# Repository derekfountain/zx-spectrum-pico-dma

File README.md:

# zx-spectrum-pico-dma

The Z80 CPU inside the ZX Spectrum is capable of DMA transfers. i.e. an external
device can take control of the buses and directly read and write the Spectrum's
memory.

To the best of my knowledge, no interface from the Spectrum's commercial era ever
took advantage of this feature, probably because it's a rather fussy thing to
work with. I wondered if it was possible for a modern microcontroller to do it.
Hence this project.

Answer: yes, it can.

# Two implementations

My first attempt at getting this DMA idea to work used my ZX Diagnostics Board
as a test platform. The fundamental problem is that an RP2040-based Pico doesn't
have enough GPIOs to do this sort of task. (It has 26, the Z80's address and data
buses immediately account for 24 of them.) I got it to work, but synchronising
the dual Picos was too slow and fussy. I eventually gave up on that and designed
a new Spectrum interface based on the RP2350B microcontroller.

The dual Pico approach is documented towards the end of this page. It's probably
not of much interest to most people. The RP2350B implementation is the more
interesting one. So let's start there.

## RP2350B Implementation

My second attempt at getting this to work involved a Raspberry Pi RP2350B microcontroller,
which has 48 GPIOs. Unlike the original RP2040, this is plenty enough for this sort of
project. I used a [Pimoroni Stamp XL](https://shop.pimoroni.com/products/rp2350-stamp-xl?variant=53521688002939).

### The Hardware

I designed a board and had it made up. It looks like this:

It's very simple, the Stamp XL runs off 5V so doesn't need any extra circuitry other
than a transistor to control the Z80's RESET line.

The RP2350 can handle the Spectrum's 5V signals as direct inputs to the GPIOs, so
the design is just to link pretty much everything on the Spectrum's rear edge connector
to a GPIO pin. The rest can be done in software.

### The Contention Problem

One of the primary reasons this DMA approach has rarely, if ever, been seen on a
Spectrum interface is the contention problem. The Spectrum's display is
generated by the ULA based on data it finds in the lower 16K of RAM. In order
to do that the ULA needs to be able to read that data from the 4116 DRAM
chips. But those chips are single ported, which means if the ULA and Z80 try
to read and/or write them simultaneously contention will happen, the ULA 
will get delayed or corrupted data, and the screen display will glitch.

The solution to this in the Spectrum circuitry is to have the ULA stop the
Z80's clock while the ULA is reading the screen memory. This solution would
also be required of any circuit which uses DMA to read or write the screen
memory. That is, if an external device takes control of the buses in order
to read or write to the screen memory, that device needs to stay clear of
the ULA's screen memory accesses otherwise contention becomes a problem.

### Timings

To do a DMA transfer into screen memory (0x4000 to 0x5AFF inclusive) it needs
to be timed precisely with the Spectrum's ULA hardware. The Spectrum hardware
in this area is simple and limited. The ULA emits a signal named INT
(because it's connected to the Z80's interrupt line) every 20ms. It does so when
the hardware is about to start drawing the screen and the TV raster is at the
top left corner.

So yes, that's simple, but it's also limited, because that's the only timing
signal the Spectrum emits. I have to work with that.

### Challenge 1 - Get it working

The initial challenge, then, is to get DMA working on the Spectrum. The aim here
is to write a single byte of data into the top left corner of the screen, with
everything else remaining stable and glitch free.

I'm going to put a dotted line - value 0x55 - in location 0x4000, so 4 little
dots appear in the corner.

### Approach

The approach used for this experimentation is as follows:

* RP2350 will raise a bus request, then wait for the Z80 to yield the buses and
respond with bus acknowledge
* RP2350 will put the address 0x4000 on the address bus
* RP2350 will put the value 0x55 on the data bus
* RP2350 will drive the signal lines in sequence to force a memory write
* RP2350 will then release the bus request signal and the Z80 can go back to
doing whatever it was doing

Compared the dual-Pico approach (scroll down if you want to know) this is pretty
straightforward, and works fine.

The key point is with the timing: this is going to happen while the ULA is
drawing the top border. Contention doesn't happen when the ULA is in 
"border time", only when the ULA is drawing the data part of the screen.
So if the DMA work can be done during border time there's no need to worry
about contention.

The other question is how long the buses need to be driven for. The first version
of my software controlled the signals with the same timing the Z80 uses. It
watched the CLK signal and responded to rising and falling clocks exactly as the
Z80 does (according to the timing diagrams in the Z80 manual). But that's not
necessary. Signals on the buses and control lines (like /MREQ and /WR) get to the
4116 DRAM chips via the Spectrum's ULA and multiplexers which pass the signals
in small numbers of nanoseconds. The 4116s themselves are the slow points, being
rated at completing a read or write in 150ns. It turns out that adding a delay
of 35 RP2350 "NOP" instructions between the /WR signal going active and inactive
is the minium requirement for successful writes. On a 150MHz RP2350 35 of the
single-cycle "NOP" instructions complete in 233ns, which seems a slower than it
needs to be. I need to investigate this. My test Spectrum for this project has been
one with a static RAM-based lower memory module, so it's hard to draw conclusions
from this hardware.

### Result

There's no point is trying to do this on an emulator, so screenshots are photos
from a real Spectrum screen.

Here's the result of the single byte write:

It's fuzzy and blurry, but, take my word for it, it does show what it should:
that splat in the in the top left corner is actually 4 individual dots. It sits
there permanently. Tapping ENTER clears the screen, but the dots flicker and
reappear immediately. They're being replaced every 20ms.

There's no way to stop this from the Z80 end. The BUSREQ/BUSACK mechanism on
the Z80 is highest priority, higher than NMI, even. If I do something on the
Spectrum which disables interrupts, the dots appear there anyway. The BEEP
command still plays a note, but it's a bit "buzzy."

### Transferring a Screenful of Data

The question that needed answering here was whether the DMA transfer would be fast
enough to move a whole ZX Spectrum display frame of data (6,912 bytes) from the RP2350
into the Spectrum's display memory in the time it takes the ULA to draw the top border.
This is where the dual-Pico approach (described below) had failed, and which I needed
to work if this DMA idea was going to be useful.

I boosted the transfer from 1 byte to 6,912 bytes and looked at the timings on the
oscilloscope. It looks like this:

The blip on the yellow line is the ULA's INT signal indicating a new frame is starting.
The cyan line is the BUSREQ signal as the RP2350 requests the Z80's bus, and the purple
line is the Z80's BUSACK signal showing the Z80 has yielded the bus. The dark blue line
is a test signal which the RP2350 is waggling as each of the 6,912 bytes is fed to the
Spectrum's lower memory. The entire duration of the transfer is about 2.3ms, which is
easily inside the 4.1ms the ULA takes to draw the top border.

## Success!

This is excellent news! Using the RP2350, with all its GPIOs, means it's easily possible
to DMA transfer a whole screen of data, flicker and contention free, from the 
microcontroller into the Spectrum inside the time it takes to draw the top border.

The next step will be to utilise this DMA transfer as part of a ZX co-processor. I have
this vague idea that a RP2350 can be used to do the sorts of things the ZX Spectrum finds
very hard, such as full screen scrolling. That's a different project, but in the meantime
I added a 50-frames-per-second, full screen scroll routine into the RP2350 code, just to
show it's possible. Here's a terribly wobbly (phone in one hand, typing on the rubber keys
with the other) animated GIF showing that scroll working:

## ZX Diagnostics Board Implementation

**TLDR: I got DMA working via a variation of my ZX Diagnostics Board which consists
of 2 Raspberry Pi Picos. But it was slow: with one Pico controlling the address bus,
and the other Pico controlling the data and control buses, a lot of time was wasted
due to the 2 Picos needing to keep sync with one another. So although it worked, it
wasn't really a usable solution. What follows is for the enthusiastic reader only.**

My first attempt at getting this working used my [ZX Diagnostics Board](https://github.com/derekfountain/zx-spectrum-diagnostics) project
as a testbed. What follows is the write up of what I did and how far I got.
Might be useful to someone, for something.

The Pico software which was working at the end of this experimentation is
tagged as v0.2.

### The Hardware

The hardware I used for this experimentation is my [ZX Diagnostics Board](https://github.com/derekfountain/zx-spectrum-diagnostics).
This board was designed to be flexible. It exposes on headers all the signals
from the Z80 (that are on the Spectrum's rear edge connector), which makes it
ideal for this sort of hardware hackery.

The main problem with doing retro-computing projects with the Pico is the limited
number of GPIOs: 26. To interface to an 8-bit micro you need to connect
GPIOs to 16 bits of address bus and 8 bits of data bus, which is 24, plus whatever
other control bus signals you need, plus user interface buttons and other things.
26 GPIOs isn't enough.

My diagnostics board interface has 2 Raspberry Pi Picos. One Pico is set up with
GPIOs connected to the data bus and several of the Z80 control bus signals, the
other Pico is set up with GPIOs connected to the 16 bits of address bus. A bit of
to and fro is required to keep them in sync, and it isn't ideal, but it does work.

I had to modify the diagnostics board slightly because when I designed it 
BUSREQ and BUSACK where not signals I connected to either Pico. So I soldered an extra
couple of wires:

* Pico 1 GPIO 16 connected to BUSREQ
* Pico 1 GPIO 17 connected to BUSACK

These Z80 signals were also wired to Pico 2 GPIO 26 and 28 respectively.

The other signals required here are IORQ, MREQ, RD and WR. These were already
connected up to Pico 1.

### The Contention Problem

One of the primary reasons this approach has rarely, if ever, been seen on a
Spectrum interface is the contention problem. The Spectrum's display is
generated by the ULA based on data it finds in the lower 16K of RAM. In order
to do that the ULA needs to be able to read that data from the 4116 DRAM
chips. But those chips are single ported, which means if the ULA and Z80 try
to read and/or write them simultaneously contention will happen, the ULA 
will get delayed or corrupted data, and the screen display will glitch.

The solution to this in the Spectrum circuitry is to have the ULA stop the
Z80's clock while the ULA is reading the screen memory. This solution would
also be required of any circuit which uses DMA to read or write the screen
memory. That is, if an external device takes control of the buses in order
to read or write to the screen memory, that device needs to stay clear of
the ULA's screen memory accesses otherwise contention becomes a problem.

### Timings

To do a DMA transfer into screen memory (0x4000 to 0x5AFF inclusive) it needs
to be timed precisely with the Spectrum's ULA hardware. The Spectrum hardware
in this area is simple and limited. The ULA emits a signal named INT
(because it's connected to the Z80's interrupt line) every 20ms. It does so when
the hardware is about to start drawing the screen and the TV raster is at the
top left corner.

So yes, that's simple, but it's also limited, because that's the only timing
signal the Spectrum emits. I have to work with that.

### Challenge 1 - Get it working

The initial challenge, then, is to get DMA working on the Spectrum. The aim here
is to write a single byte of data into the top left corner of the screen, with
everything else remaining stable and glitch free.

I'm going to put a dotted line - value 0x55 - in location 0x4000, so 4 little
dots appear in the corner.

### Approach

The approach used for this experimentation is as follows:

* Pico1 will raise a bus request, then wait for the Z80 to yield the buses and
respond with bus acknowledge
* Pico1 will tell Pico2 - which controls the address bus - to put the address
0x4000 on the address bus
* Pico1 will put the value 0x55 on the data bus
* Pico1 will drive the signal lines in sequence to force a memory write
* When the byte is written, Pico1 will tell Pico2 to stop driving the address
bus, and will itself stop driving the data and control bus lines
* Pico1 will then release the bus request signal and the Z80 can go back to
doing whatever it was doing

The key point is with the timing: this is going to happen while the ULA is
drawing the top border. Contention doesn't happen when the ULA is in 
"border time", only when the ULA is drawing the data part of the screen.
So if the DMA work can be done during border time there's no need to worry
about contention.

The other question is how long the buses need to be driven for. The first version
of my software controlled the signals with the same timing the Z80 uses. It
watched the CLK signal and responded to rising and falling clocks exactly as the
Z80 does (according to the timing diagrams in the Z80 manual). But that's not
necessary. Signals on the buses and control lines (like /MREQ and /WR) get to the
4116 DRAM chips via the Spectrum's ULA and multiplexers which pass the signals
in small numbers of nanoseconds. The 4116s themselves are the slow points, being
rated at completing a read or write in 150ns. It turns out that adding a delay
of 19 RP2040 "NOP" instructions between the /WR signal going active and inactive
is the minium requirement for successful writes. On a 125MHz RP2040 19 of the
single-cycle "NOP" instructions complete in 152ns, which seems to add up.

### Result

There's no point is trying to do this on an emulator, so screenshots are photos
from a real Spectrum screen.

Here's the result of the single byte write:

It's fuzzy and blurry, but, take my word for it, it does show what it should:
that splat in the in the top left corner is actually 4 individual dots. It sits
there permanently. Tapping ENTER clears the screen, but the dots flicker and
reappear immediately. They're being replaced every 20ms.

There's no way to stop this from the Z80 end. The BUSREQ/BUSACK mechanism on
the Z80 is highest priority, higher than NMI, even. If I do something on the
Spectrum which disables interrupts, the dots appear there anyway. The BEEP
command still plays a note, but it's a bit "buzzy."

### Signals Analysis

Here's the trace from the oscilloscope:

Yellow is the ULA's INT signal, which is pulled low every 20ms. The RP2040 on the
Pico is programmed with a hardware interrupt when that line goes low. The handler
function asserts the BUSREQ "bus request" signal, which is the light blue line.
BUSREQ goes low approximately 2.5 microseconds after INT goes low, that being the
time it takes for the RP2040 to respond to a GPIO interrupt.

The RP2040 code spins looking for BUSACK "bus acknowledge" to go low. There is a
variable length pause while the Z80 finishes the instruction it's running, and then
it pulls BUSACK low. That's the purple line. In the shown example, BUSACK goes low
about 600ns after BUSREQ went low, but this varies. The purple line flickers on
the 'scope.

When the BUSACK goes low the DMA process takes place. The dark blue line shows a high
pulse while the DMA is running. It takes just about 1uS to drive a transfer of one
byte to the Spectrum's memory. This includes the wasteful but necessary synchronisation
with the other Pico which drives the address bus.

As soon as the DMA is complete (blue line falling) the BUSREQ line is released
(light blue line rising). The Z80 retakes control (purple line rising as it turns
off the BUSACK signal) and the process is complete. End of DMA to the Z80 having
control again is about 150ns.

The Z80 "loses" the period of the purple line being low, which is about 1.6uS.

### Challenge 2 - More data

Proving a single byte can be written into Spectrum memory is gratifying, but not really
very useful. Next step is to try writing more data. Let's try 2KB. This requires
advancing the value on the address bus with each byte written. Here's the screen,
again a bit fuzzy, but correctly showing what it should:

That pattern is permanent, and since it takes a lot longer to transfer in than the
single byte example, the BEEP is a lot buzzier. Some games, presumably those that
don't read back their screen data, still work. Jetpac, for example, still runs quite
happily even though you can't see what you're doing.

The trace from the oscilloscope:

This all looks OK, but a problem is starting to appear. It takes the ULA 224 Z80 T-states
to draw a single line of the screen, and the top border is 64 lines high. So  Spectrum "top
border time" is 64 line times, which is 14,336 T states. A T is 1/3,500,000 of a second so
top border time is 0.004096 of a second, or a smidge over 4ms. The oscilloscope trace shows
the DMA time for 2048 bytes (dark blue line) to be just about 1,800uS, or 1.8ms. That's to
DMA one third of a Spectrum screen. A full screen will take 5.4ms, not including the time
taken to transfer the attributes data which is another 768 bytes (32x24 bytes).

I put a trace pulse in the code which drives the address bus:

This line goes high at the point the required address is loaded onto the Z80's address
bus, then goes low again when the address bus is relinquished. It takes about 500ns,
so that's the time for writing one byte. On top of that, there's quite a bit of overhead as
the Picos signal and synchronise with each other, all of which could be removed if I can use a
single microcontroller with enough GPIOs to do everything itself. But I don't have one
of those, and there's no way to avoid the synchronisation at the moment.

This is disappointing. DMA can only really be done in border time, to avoid contention. (I
saw plenty of contention while I was experimenting with this. The screen glitches all over
the place.) I was hoping to be able to do full screen scrolling in the RP2040, for example,
but clearly if the screen can't be quickly transferred back into the Spectrum after processing
then it's not much use.

I figured it might be possible to interweave the DMA with the CPU's CLK signal. The CLK is
generated by the ULA, so when the CLK signal goes flat that means the ULA is accessing
RAM. But that means somehow accessing the CLK such that when it stops pulsing the RP2040
stops the DMA. It might be possible to do that? Perhaps a PIO watching the CLK signal
and indicating to the core when the CLK stops? I didn't try it but it might work.

### Challenge 3 - A Screenful

Next step is to try transferring a full screen of data into the Spectrum. This is the
underlying requirement. If an RP2040 is to be used to do full screen scrolling or other such
things it needs to be able to transfer the results back into the Spectrum at 50fps. If it
can't there's only so much point in doing it. You might as well do the job on the Spectrum.

So this next experiment does what the previous ones do: transfer a block of data into the
Spectrum at the point of the ULA's INTerrupt, when the ULA is drawing the top border. The
data block for a full screen is 6,912 byte - 6,144 for the graphics, plus 768 for the 
attributes.

Here's how the result looks:

The screen fills as expected, but there's shimmering and glitching, and the Spectrum hangs.

The oscilloscope trace looks like this:

This is at 1ms per division, the entire DMA trace takes just over 6ms. Top border time is
4ms, this is causing contention, hence the flickering.

I think the Spectrum is hanging because the Z80 is getting incorrect data from the lower
RAM, which is where it stores system information. The contention doesn't just affect the
screen memory, it affects all the lower 16K. I'm not entirely sure what's going on with this
hangup to be honest, but it doesn't really matter. A full screen DMA isn't possible in top
border time.

#### Try Bottom Border Time

The Spectrum's border is in two pieces, top and bottom, separated by the screen image of course.
If I can start the DMA at the point the ULA starts to draw the bottom border (i.e. just as it's
finished drawing line 192 of the screen itself) then I get bottom border time, followed by top
border time, before the ULA wants to access the RAM again (in order for it to start drawing the
top line of the screen).

Lower border is 56 lines at 224Ts per line, which is 12,544 Ts. On the 3.5MHz Z80 12,544 T-states
takes 0.003584 seconds, or 3.584ms. So if I can time it perfectly, I get 3.584ms of bottom
border time, followed by 4.096ms of top border time, to complete the DMA without causing
contention. That's 7.68ms, which should be enough to complete the full screen DMA which takes
just over 6ms.

The problem is that there's no timing signal or indication that the ULA has completed drawing the
data area and is about to start drawing the bottom border. The only option is to do it on a timer.
To hit the start of lower border time from the moment INT fires, I need 64 lines of top border,
plus 192 lines of screen, That's 228 lines from INT to the start of the lower border. At 224Ts per
line, 228 lines is 64,512 Ts. That's 18.432ms.

The approach here is to start a timer for 18,432uS in the INT handler, then go back to sleep. The
DMA actually happens when the second timer expires:

Here, yellow shows is the INT signal, which is the point when the 18,432uS timer is started. Light
blue shows the BUSREQ signal, which is the start of the DMA process. The 'scope's cursor shows the
time difference between the two:

The gap is 18.4ms, which looks right. I'm hoping the 0.032ms offset is a measuring error.

The above images are based on a single byte DMA, which worked. But something very odd started
happening in the RP2040 when I made the transfer larger. It seems the Pico SDK wouldn't set up the
next alarm call function until the current one finished executing. So the first INT would arrive
and its handler would set the 18.4ms timer running. When that expired the DMA would start. But with
a large DMA, the transfer would still be running when the next INT arrived. With the alarm timer
still running and DMAing bytes to the Spectrum, either the INT handler didn't run, or it wouldn't
set up the alarm handler correctly. After a lot of messing about I found that doing the DMA
transfer from the second core of the RP2040 made the problem go away and the screen filled as
expected:

Here's the oscilloscope trace:

The first INT is where the orange trigger cursor is on the yellow line. That causes a handler
to run which sets up an alarm to call the DMA function 18.4ms seconds later. The DMA function
for that INT is the next one on the light blue line - i.e. not the one directly below the INT,
but the one nearly 4 divisions later, to the right. As you can see, the next INT arrives during
the DMA process, which sets up the next alarm while the current one finishes, and so on.

## Fail

With the dual core hack in place, this worked! Hurrah! Only it didn't, because although the DMA
worked correctly, and at just about spot on 6.0ms was plenty quick enough to be inside the 7.68ms
dual borders time, the Spectrum hanged every time. It took me an age to work out why, but it's
obvious when you know: the INT signal is being generated correctly by the ULA, and the Pico is
responding to it correctly, but because the bus request is active when the next INT comes in
the Z80 (which is effectively sitting suspended) doesn't see it. So the Spectrum's not getting to
run its interrupt routine which does all sort of useful stuff like reading the keyboard.

It might still be possible to make this work. Some of the DMA transfer could be done in lower
border time, and as long as that was finished and the BUSREQ removed by the time the next INT
arrived, it might then be possible to do the rest of the DMA transfer in top border time. i.e. do it
in two portions. But for BASIC to work properly the top border transfer needs to be well clear of
the Spectrum ROM's interrupt handler routine. It's messy and fiddly and not really the solution
I'm after.

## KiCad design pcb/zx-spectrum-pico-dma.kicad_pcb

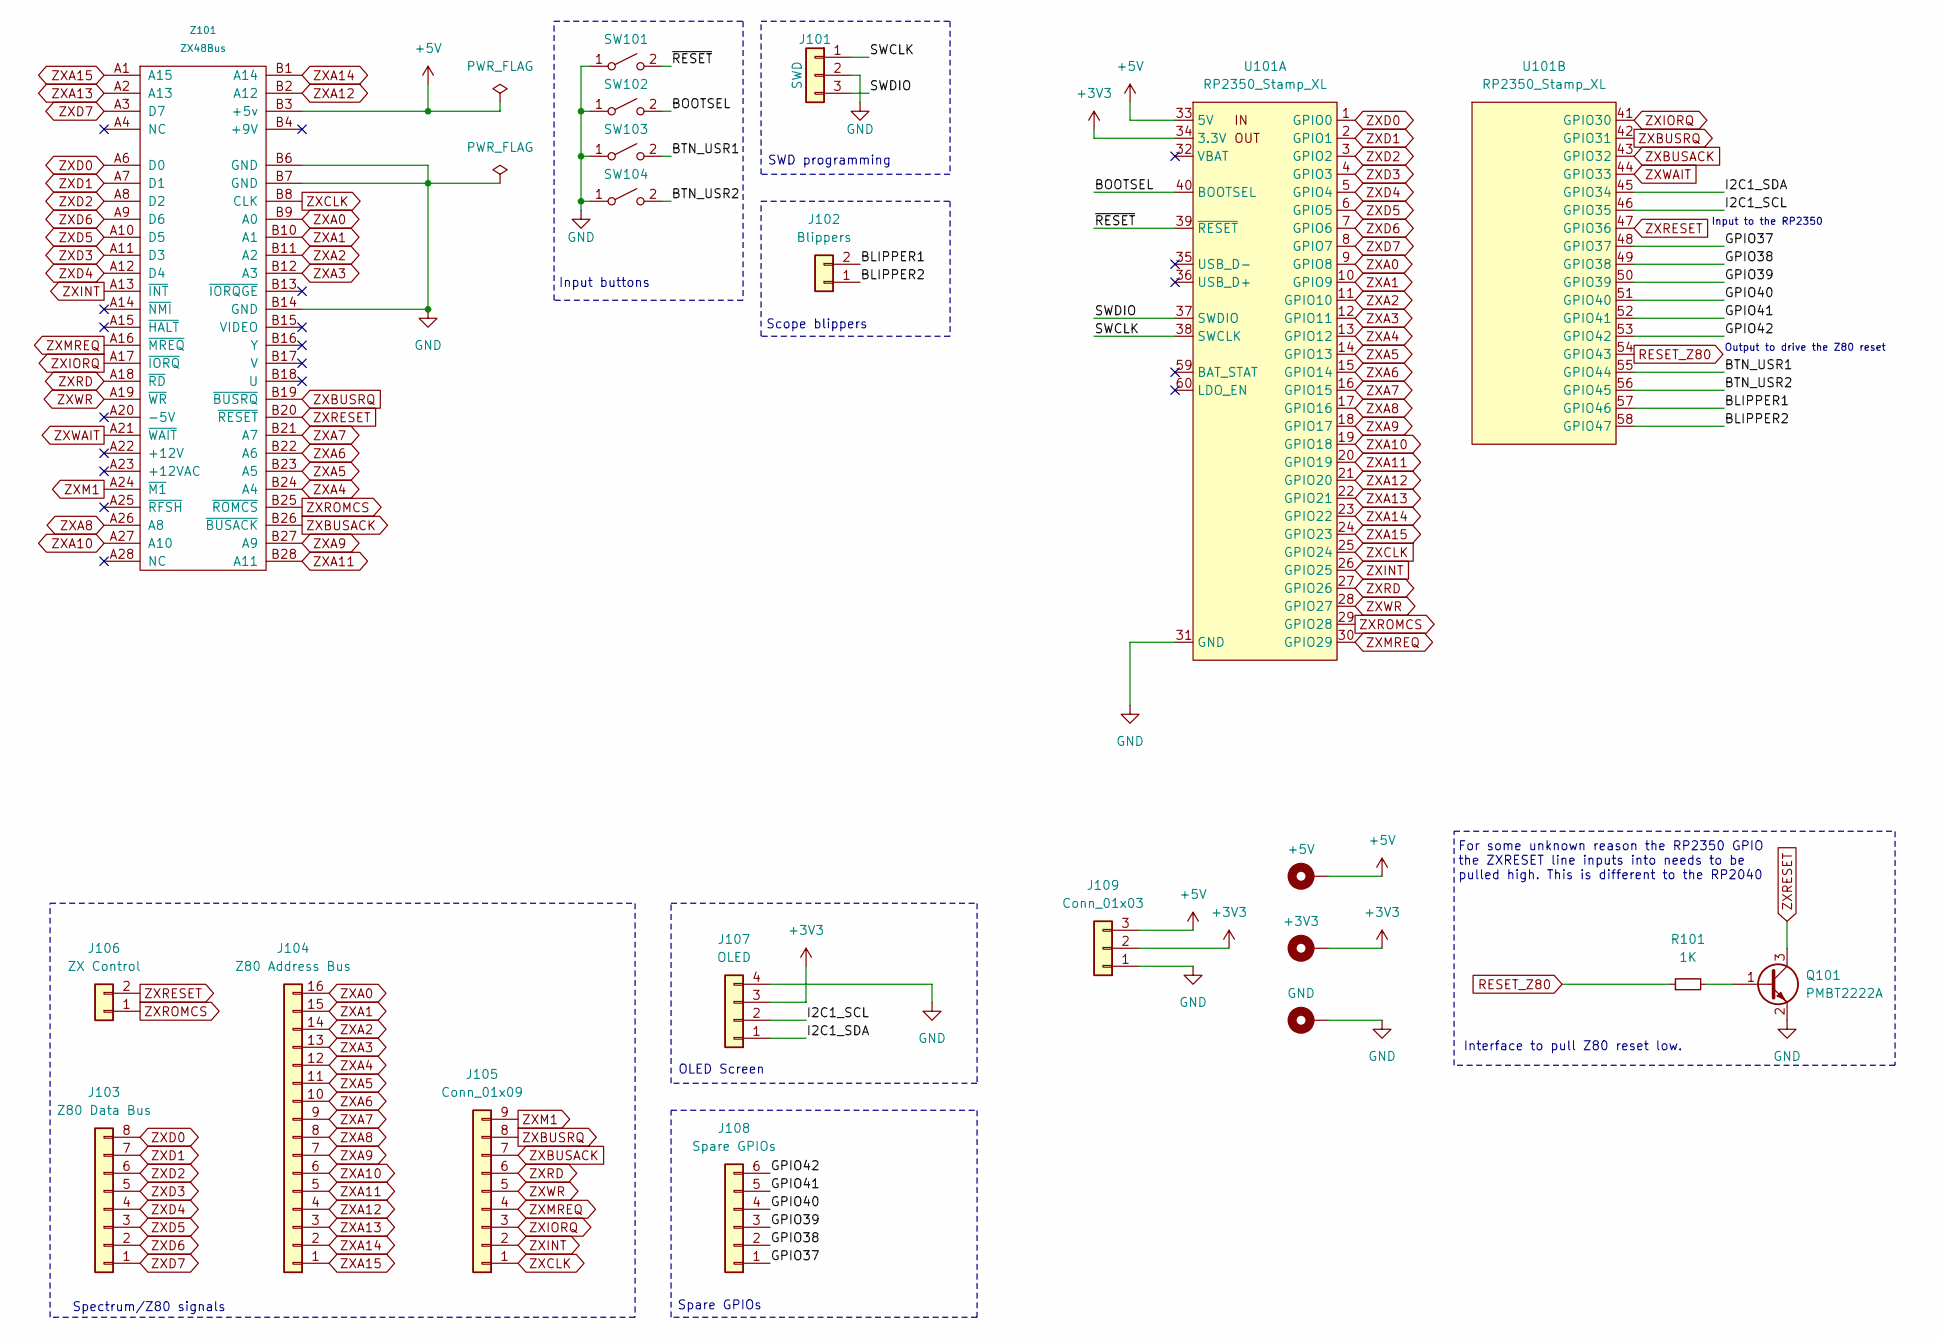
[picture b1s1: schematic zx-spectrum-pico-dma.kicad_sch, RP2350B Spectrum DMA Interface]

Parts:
H101: +5V; MountingHole_2.2mm_M2_Pad
H102: +3V3; MountingHole_2.2mm_M2_Pad
H103: GND; MountingHole_2.2mm_M2_Pad
J101: SWD; PinHeader_1x03_P2.54mm_Vertical; LCSC C7433424
J102: Blippers; PinHeader_1x02_P2.54mm_Vertical
J103: Z80 Data Bus; PinHeader_1x08_P2.54mm_Vertical
J104: Z80 Address Bus; PinHeader_1x16_P2.54mm_Vertical
J105: Conn_01x09; PinHeader_1x09_P2.54mm_Vertical
J106: ZX Control; PinHeader_1x02_P2.54mm_Vertical
J107: OLED; PinHeader_1x04_P2.54mm_Vertical
J108: Spare GPIOs; PinHeader_1x06_P2.54mm_Vertical
J109: Conn_01x03; PinHeader_1x03_P2.54mm_Vertical
Q101: PMBT2222A; TSOT-23_HandSoldering
R101: 1K; R_1206_3216Metric_Pad1.30x1.75mm_HandSolder
SW101: BTN_RESET; SW_PUSH_6mm_H4.3mm; LCSC C561514
SW102: BTN_BOOTSEL; SW_PUSH_6mm_H4.3mm; LCSC C561514
SW103: BTN_USR1; SW_PUSH_6mm_H4.3mm; LCSC C561514
SW104: BTN_USR2; SW_PUSH_6mm_H4.3mm; LCSC C561514
U101: RP2350_Stamp_XL; RP2xxx_Stamp_XL_THT
Z101: ZX48Bus; Spectrum_Edge_Connector

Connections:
+3V3: H102.1, J107.3, J109.2, U101.34 (3.3V)
+5V: H101.1, J109.3, U101.33 (5V), Z101.B3 (+5v)
/BLIPPER1: J102.2, U101.57 (GPIO46)
/BLIPPER2: J102.1, U101.58 (GPIO47)
/BOOTSEL: SW102.2 (B), U101.40 (BOOTSEL)
/BTN_USR1: SW103.2 (B), U101.55 (GPIO44)
/BTN_USR2: SW104.2 (B), U101.56 (GPIO45)
/GPIO37: J108.1, U101.48 (GPIO37)
/GPIO38: J108.2, U101.49 (GPIO38)
/GPIO39: J108.3, U101.50 (GPIO39)
/GPIO40: J108.4, U101.51 (GPIO40)
/GPIO41: J108.5, U101.52 (GPIO41)
/GPIO42: J108.6, U101.53 (GPIO42)
/I2C1_SCL: J107.2, U101.46 (GPIO35)
/I2C1_SDA: J107.1, U101.45 (GPIO34)
/SWCLK: J101.1, U101.38 (SWCLK)
/SWDIO: J101.3, U101.37 (SWDIO)
/~RESET: SW101.2 (B), U101.39 (~RESET)
GND: H103.1, J101.2, J107.4, J109.1, Q101.2 (E), SW101.1 (A), SW102.1 (A), SW103.1 (A), SW104.1 (A), U101.31 (GND), Z101.B6 (GND), Z101.B7 (GND), Z101.B14 (GND)
unnamed: Q101.1 (B), R101.2
RESET_Z80: R101.1, U101.54 (GPIO43)
ZXA0: J104.16, U101.9 (GPIO8), Z101.B9 (A0)
ZXA1: J104.15, U101.10 (GPIO9), Z101.B10 (A1)
ZXA2: J104.14, U101.11 (GPIO10), Z101.B11 (A2)
ZXA3: J104.13, U101.12 (GPIO11), Z101.B12 (A3)
ZXA4: J104.12, U101.13 (GPIO12), Z101.B24 (A4)
ZXA5: J104.11, U101.14 (GPIO13), Z101.B23 (A5)
ZXA6: J104.10, U101.15 (GPIO14), Z101.B22 (A6)
ZXA7: J104.9, U101.16 (GPIO15), Z101.B21 (A7)
ZXA8: J104.8, U101.17 (GPIO16), Z101.A26 (A8)
ZXA9: J104.7, U101.18 (GPIO17), Z101.B27 (A9)
ZXA10: J104.6, U101.19 (GPIO18), Z101.A27 (A10)
ZXA11: J104.5, U101.20 (GPIO19), Z101.B28 (A11)
ZXA12: J104.4, U101.21 (GPIO20), Z101.B2 (A12)
ZXA13: J104.3, U101.22 (GPIO21), Z101.A2 (A13)
ZXA14: J104.2, U101.23 (GPIO22), Z101.B1 (A14)
ZXA15: J104.1, U101.24 (GPIO23), Z101.A1 (A15)
ZXBUSACK: J105.7, U101.43 (GPIO32), Z101.B26 (~BUSACK)
ZXBUSRQ: J105.8, U101.42 (GPIO31), Z101.B19 (~BUSRQ)
ZXCLK: J105.1, U101.25 (GPIO24), Z101.B8 (CLK)
ZXD0: J103.8, U101.1 (GPIO0), Z101.A6 (D0)
ZXD1: J103.7, U101.2 (GPIO1), Z101.A7 (D1)
ZXD2: J103.6, U101.3 (GPIO2), Z101.A8 (D2)
ZXD3: J103.5, U101.4 (GPIO3), Z101.A11 (D3)
ZXD4: J103.4, U101.5 (GPIO4), Z101.A12 (D4)
ZXD5: J103.3, U101.6 (GPIO5), Z101.A10 (D5)
ZXD6: J103.2, U101.7 (GPIO6), Z101.A9 (D6)
ZXD7: J103.1, U101.8 (GPIO7), Z101.A3 (D7)
ZXINT: J105.2, U101.26 (GPIO25), Z101.A13 (~INT)
ZXIORQ: J105.3, U101.41 (GPIO30), Z101.A17 (~IORQ)
ZXM1: J105.9, Z101.A24 (~M1)
ZXMREQ: J105.4, U101.30 (GPIO29), Z101.A16 (~MREQ)
ZXRD: J105.6, U101.27 (GPIO26), Z101.A18 (~RD)
ZXRESET: J106.2, Q101.3 (C), U101.47 (GPIO36), Z101.B20 (~RESET)
ZXROMCS: J106.1, U101.29 (GPIO28), Z101.B25 (~ROMCS)
ZXWAIT: U101.44 (GPIO33), Z101.A21 (~WAIT)
ZXWR: J105.5, U101.28 (GPIO27), Z101.A19 (~WR)

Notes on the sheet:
Input to the RP2350
Input buttons
For some unknown reason the RP2350 GPIO the ZXRESET line inputs into needs to be pulled high. This is different to the RP2040
Spare GPIOs
Interface to pull Z80 reset low.
Scope blippers
OLED Screen
Output to drive the Z80 reset
SWD programming
Spectrum/Z80 signals

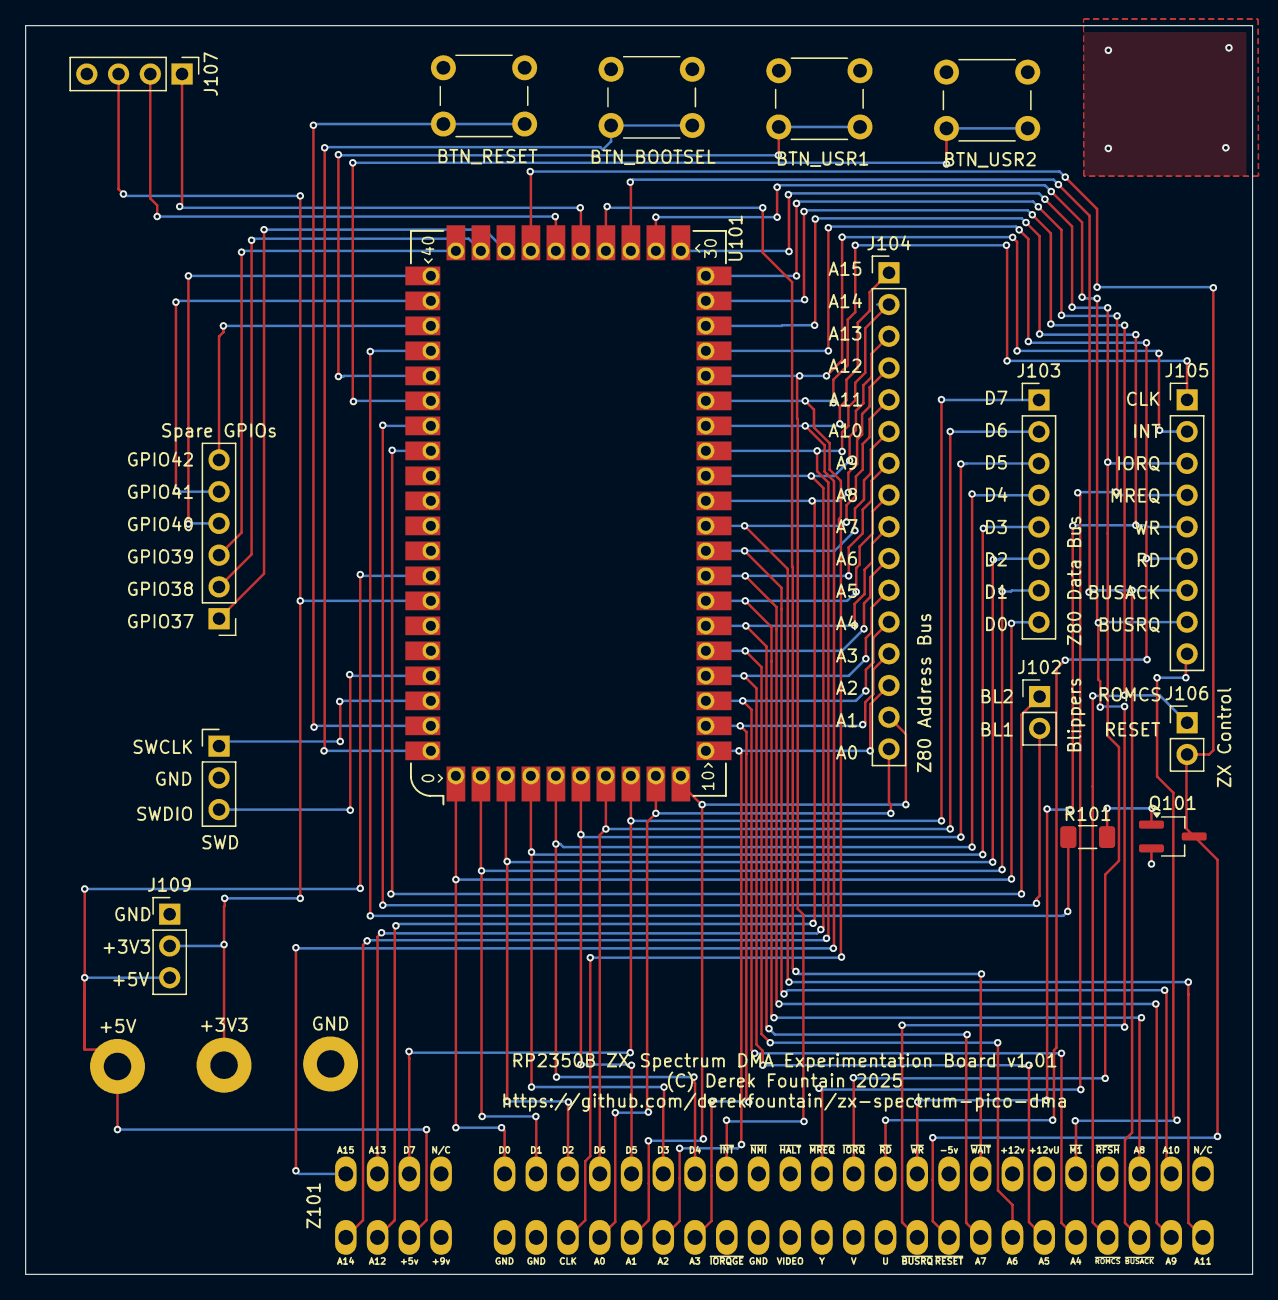
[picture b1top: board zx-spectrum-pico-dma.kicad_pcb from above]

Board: 2 copper layers, 98.2 x 99.9 mm, 20 parts (0 on the bottom side), 57 nets.

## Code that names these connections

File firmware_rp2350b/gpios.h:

/*
 * GPIOs for RP2350 Stamp XL
 *
 * These need to match the hardware design.
 */

#ifndef __GPIOS_H
#define GPIOS_H

/* Test signals to scope */
#define GPIO_BLIPPER1     46
#define GPIO_BLIPPER2     47

/* Take over the Spectrum's ROM */
#define GPIO_ROMCS        28

/*
 * This pin is the output connected to the base of Q101.
 * Driving it positive pulls ZXRESET low
 */
#define GPIO_RESET_Z80    43

/*
 * This pin is an input to the RP2350. It's the Z80's
 * /RESET signal and is here so the RP2350 can tell when
 * the Spectrum is being reset. This isn't an output for
 * resetting the Spectrum, GPIO_RESET_Z80 does that.
*/
#define GPIO_Z80_RESET    36

/* Z80 Control bus */
#define GPIO_Z80_CLK      24
#define GPIO_Z80_INT      25
#define GPIO_Z80_RD       26
#define GPIO_Z80_WR       27
#define GPIO_Z80_MREQ     29
#define GPIO_Z80_IORQ     30
#define GPIO_Z80_BUSREQ   31
#define GPIO_Z80_BUSACK   32
#define GPIO_Z80_WAIT     33

/* Z80 Data bus */
#define GPIO_DBUS_D0      0
#define GPIO_DBUS_D1      1
#define GPIO_DBUS_D2      2
#define GPIO_DBUS_D3      3
#define GPIO_DBUS_D4      4
#define GPIO_DBUS_D5      5
#define GPIO_DBUS_D6      6
#define GPIO_DBUS_D7      7

#define GPIO_DBUS_BITMASK 0x000000FF

/* Z80 Address bus */
#define GPIO_DBUS_A0      8
#define GPIO_DBUS_A1      9
#define GPIO_DBUS_A2      10
#define GPIO_DBUS_A3      11
#define GPIO_DBUS_A4      12
#define GPIO_DBUS_A5      13
#define GPIO_DBUS_A6      14
#define GPIO_DBUS_A7      15
#define GPIO_DBUS_A8      16
#define GPIO_DBUS_A9      17
#define GPIO_DBUS_A10     18
#define GPIO_DBUS_A11     19
#define GPIO_DBUS_A12     20
#define GPIO_DBUS_A13     21
#define GPIO_DBUS_A14     22
#define GPIO_DBUS_A15     23

#define GPIO_ABUS_BITMASK 0x00FFFF00

#endif

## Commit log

2024-11-06 initial release, changes a byte in the display file
2024-11-08 rename LINKOUT pico to pico signal
2024-11-10 use API functions to handle the GPIO driving better
2024-11-10 tidy up GPIO signals on the Pico2 side
2024-11-10 change pico1 to work on a hardware interrupt on INT. loop in pico2 to fill top third
2024-11-11 fix bug causing most on screen corruption, there's still something else not quite right
2024-11-12 restore to working single byte DMA after going a bit astray
2024-11-12 putting 256 bytes into the RAM correctly in about 300uS, zx not happy
2024-11-12 add a start up synchronisation signal
2024-11-12 2KB transfer takes about 2.25ms, still an intermittent startup problem
2024-11-12 solder wires to expore BUSREQ and BUSACK to pico2. works for 1 byte, not for many
2024-11-13 2 byte DMA working, takes approx 3uS
2024-11-13 2048 byte DMA working, takes approx 3mS which is too slow. top border time is 4ms
2024-11-14 various workings trying to get the WR pause as short as possible
2024-11-14 tidy up all the workings
2024-11-14 sync to the start of lower border to gain more non-contended time
2024-11-16 full screen DMA stable at 25fps
2024-11-16 start the documentation
2024-11-18 2KB transfer documented in readme
2024-11-19 dual core hack to get the full screen transfer working. which fails, i'll back this out
2024-11-20 start a rp2350b based pcb
2024-11-21 pull in board from zx diagnostics project
2024-11-21 add ground area
2024-11-23 flesh out initial schematic
2024-11-23 more layout work
2024-11-29 thought about barrel jacks to control zx power, decided against. final tidyups
2024-11-29 first fabrication
2024-12-07 remove the multicore experiment
2024-12-07 finalise and mothball the dual pico code, need to start on RP2350B version
2024-12-07 start with blink example code for the rp2350b on the stamp XL
2025-02-13 first draft of rp2350b DMA code
2025-02-15 zx starts with rp2350 running this code
2025-02-23 crude timings, but the DMA is working
2025-02-23 6912 byte DMA now working
2025-02-23 reset GPIO RP2350? workaround in place, firmware is working
2025-02-26 update schematic to reflect the revised RESET labelling
2025-02-26 screen mirror working
2025-02-27 tidy ups, comments
2025-02-28 add a scrolling demo, just to show it works
2025-03-01 add photos of the board
2025-03-14 add M1 from edge connector to a pin, it's needed on the logic analyser so I need to make it available
2025-03-14 add a 3-pin supplies header, the mounting points aren't easy to attach a clip to
